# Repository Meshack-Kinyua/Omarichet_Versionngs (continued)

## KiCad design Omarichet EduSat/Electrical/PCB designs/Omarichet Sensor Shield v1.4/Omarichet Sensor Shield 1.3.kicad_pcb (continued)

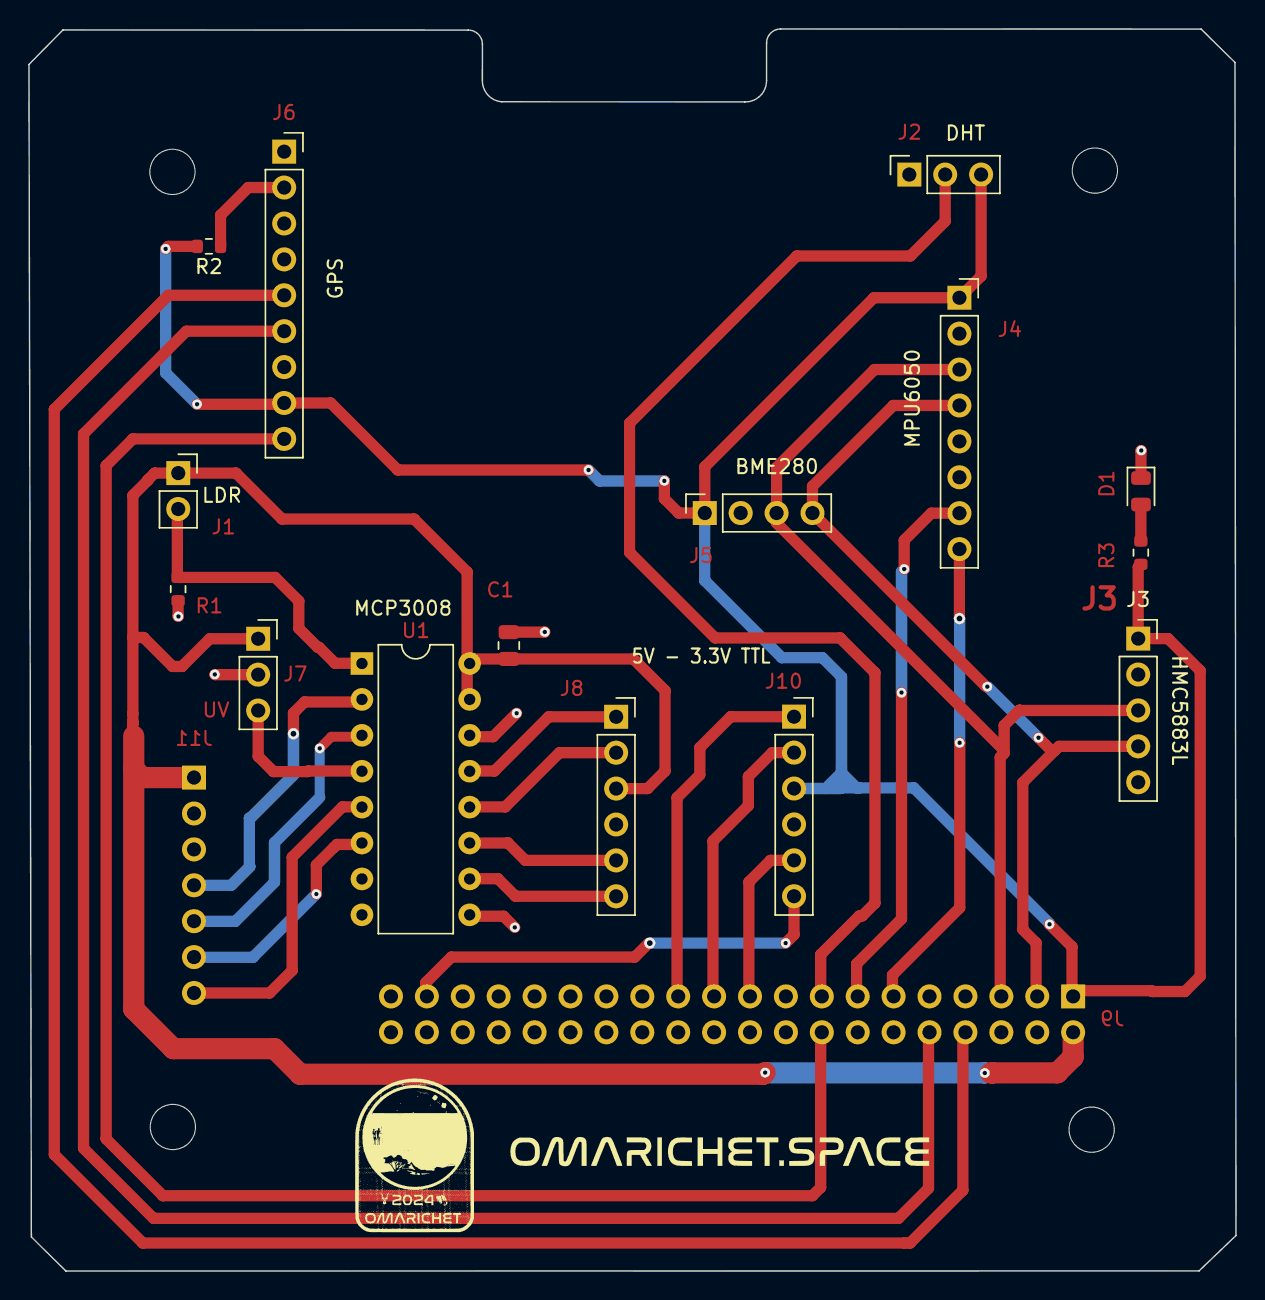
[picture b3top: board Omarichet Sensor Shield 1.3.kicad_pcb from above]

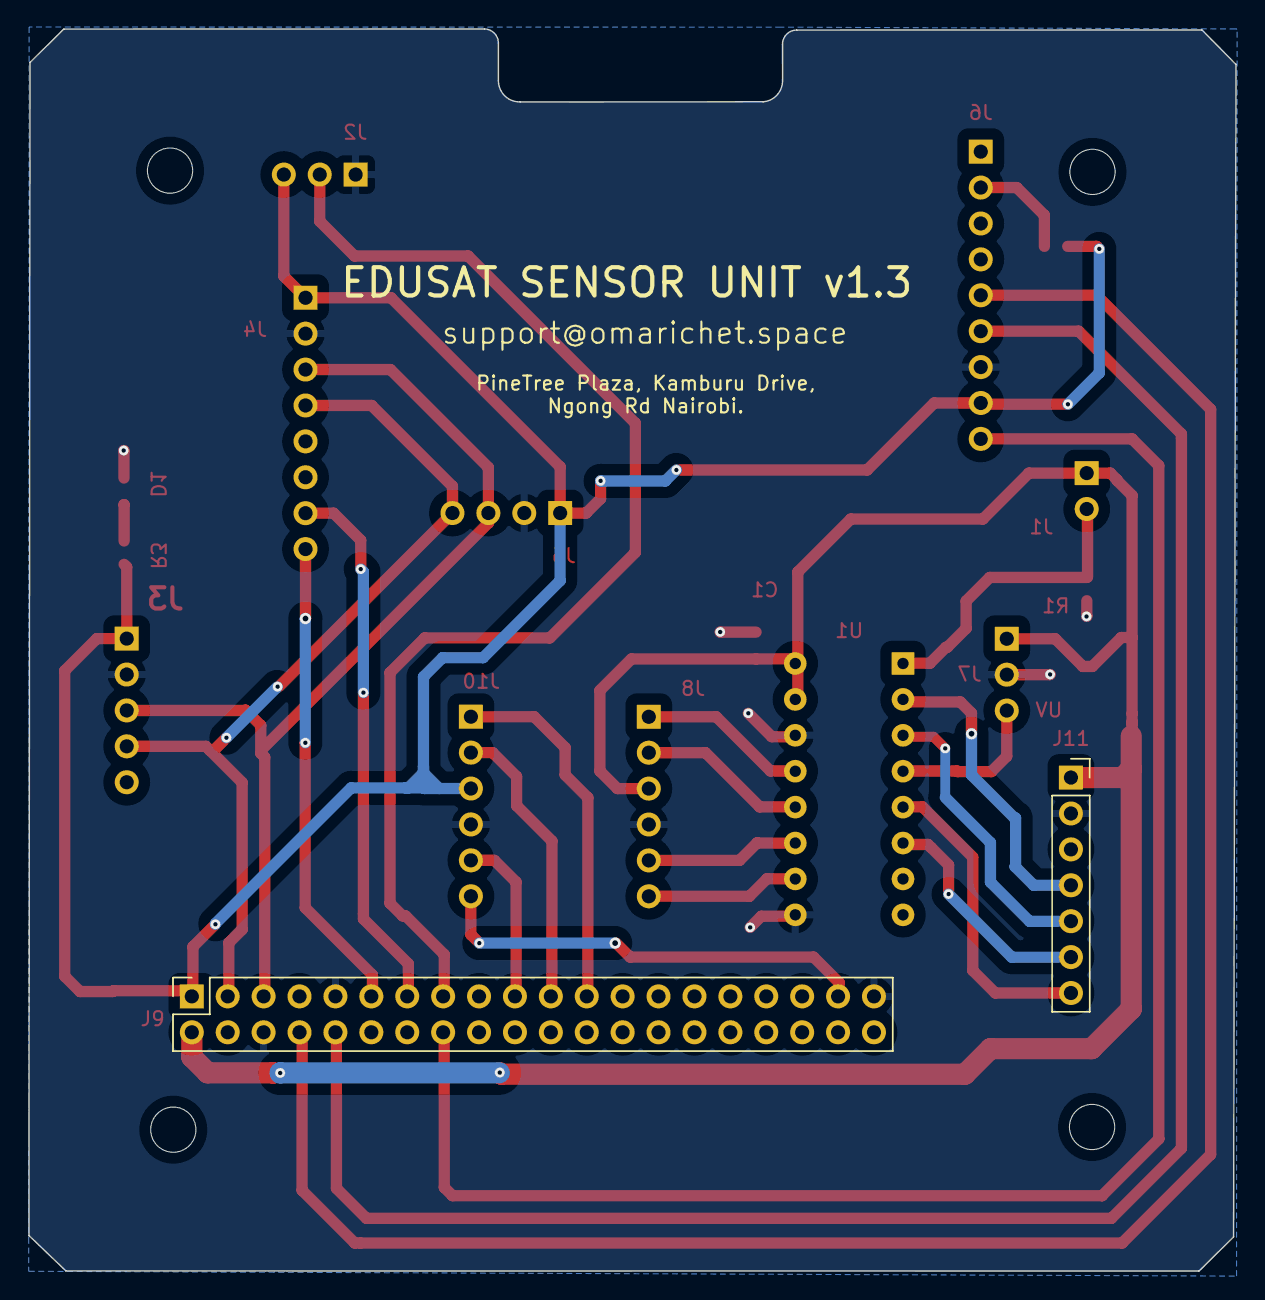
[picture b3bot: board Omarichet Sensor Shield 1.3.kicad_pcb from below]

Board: 2 copper layers, 85.4 x 87.9 mm, 21 parts (2 on the bottom side), 27 nets.

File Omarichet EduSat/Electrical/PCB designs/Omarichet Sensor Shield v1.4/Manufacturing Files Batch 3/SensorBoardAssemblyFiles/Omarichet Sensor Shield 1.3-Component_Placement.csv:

Ref,Val,Package,PosX,PosY,Rot,Side
"J9","Conn_02x20_Odd_Even","PinSocket_2x20_P2.54mm_Vertical",-159.670000,-129.990000,90.000000,bottom
"J11","Conn_01x07_Female","PinSocket_1x07_P2.54mm_Vertical",-97.475000,-114.510000,180.000000,bottom
"C1","100n","C_0805_2012Metric",119.750000,-105.170000,90.000000,top
"D1","LED","LED_0805_2012Metric",164.470000,-94.257500,-90.000000,top
"J1","Conn_01x02_Light","PinSocket_1x02_P2.54mm_Vertical",96.360000,-92.970000,0.000000,top
"J2","Conn_01x03_DHT","PinSocket_1x03_P2.54mm_Vertical",148.080000,-71.850000,90.000000,top
"J3","Conn_01x05_HMC5883L","PinSocket_1x05_P2.54mm_Vertical",164.275000,-104.680000,0.000000,top
"J4","Conn_01x08_mpu6050","PinSocket_1x08_P2.54mm_Vertical",151.625000,-80.565000,0.000000,top
"J5","Conn_01x04_BME280","PinSocket_1x04_P2.54mm_Vertical",133.610000,-95.795000,90.000000,top
"J6","Conn_01x09_GPS","PinSocket_1x09_P2.54mm_Vertical",103.855000,-70.230000,0.000000,top
"J7","Conn_01x03_GUVA-S12SD","PinSocket_1x03_P2.54mm_Vertical",102.015000,-104.690000,0.000000,top
"J8","Conn_01x06_LLCA","PinSocket_1x06_P2.54mm_Vertical",127.340000,-110.210000,0.000000,top
"J10","Conn_01x06_LLCB","PinSocket_1x06_P2.54mm_Vertical",139.925000,-110.205000,0.000000,top
"R1","10k","R_0603_1608Metric",96.350000,-101.175000,-90.000000,top
"R2","10K","R_0603_1608Metric",98.530000,-76.930000,180.000000,top
"R3","R","R_0603_1608Metric",164.460000,-98.600000,90.000000,top
"U1","MCP3008","DIP-16_W7.62mm",109.356000,-106.441000,0.000000,top

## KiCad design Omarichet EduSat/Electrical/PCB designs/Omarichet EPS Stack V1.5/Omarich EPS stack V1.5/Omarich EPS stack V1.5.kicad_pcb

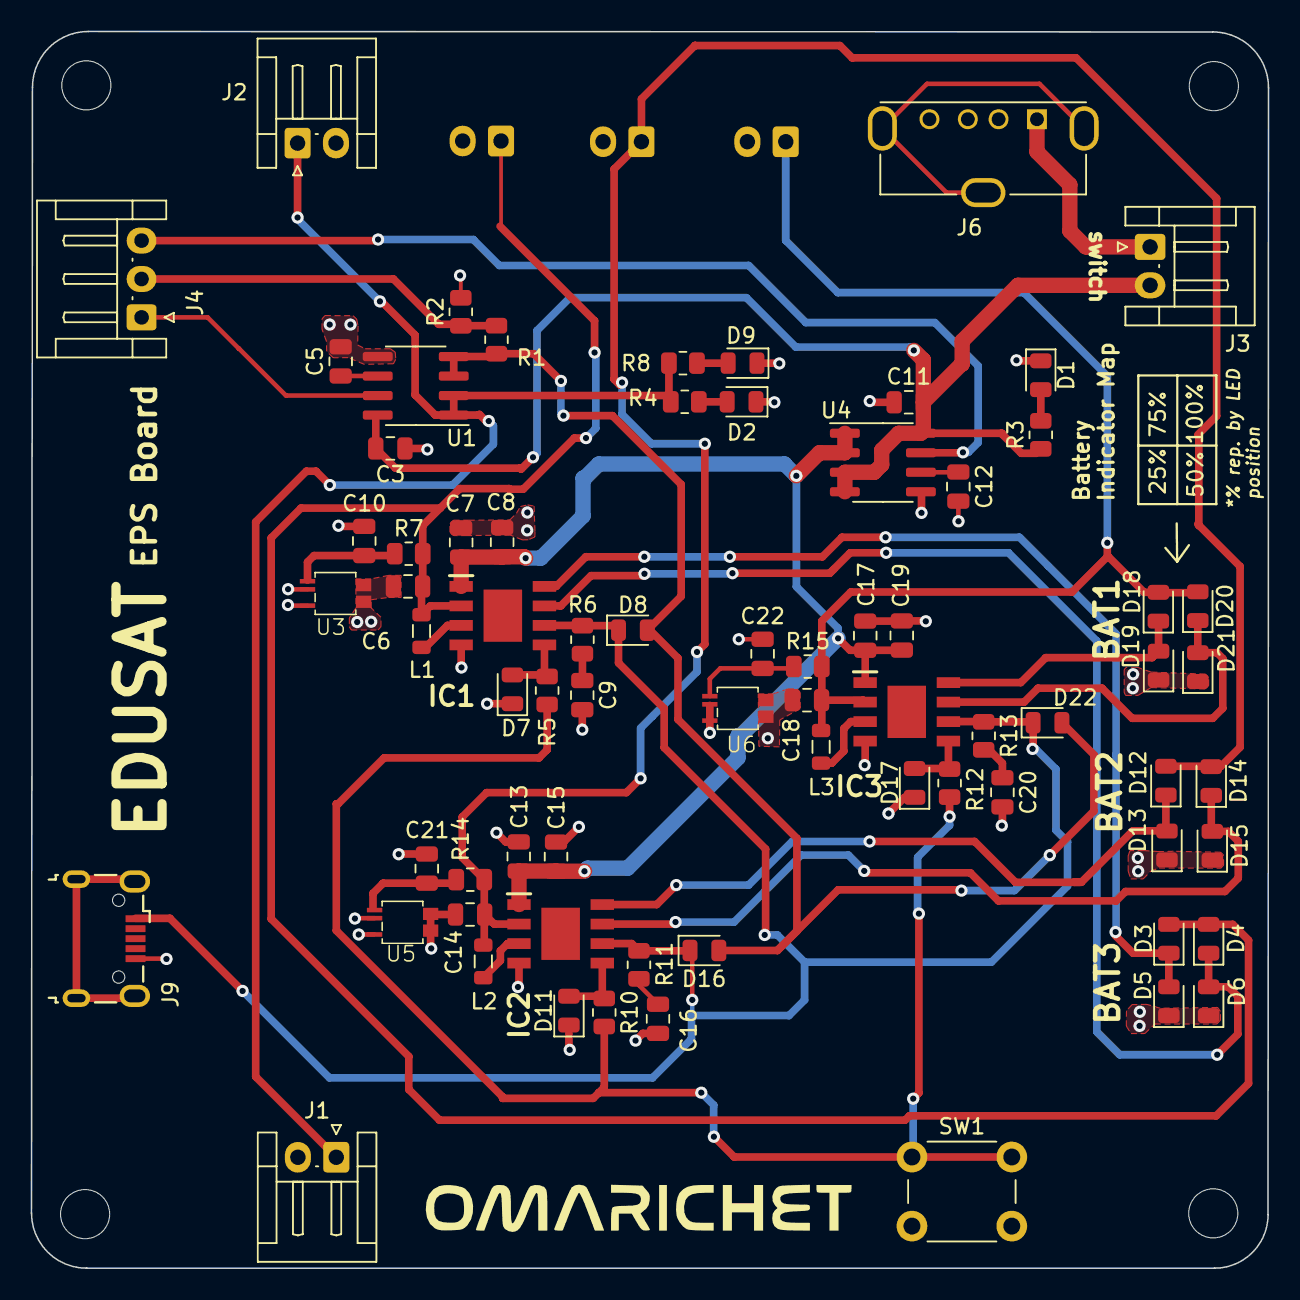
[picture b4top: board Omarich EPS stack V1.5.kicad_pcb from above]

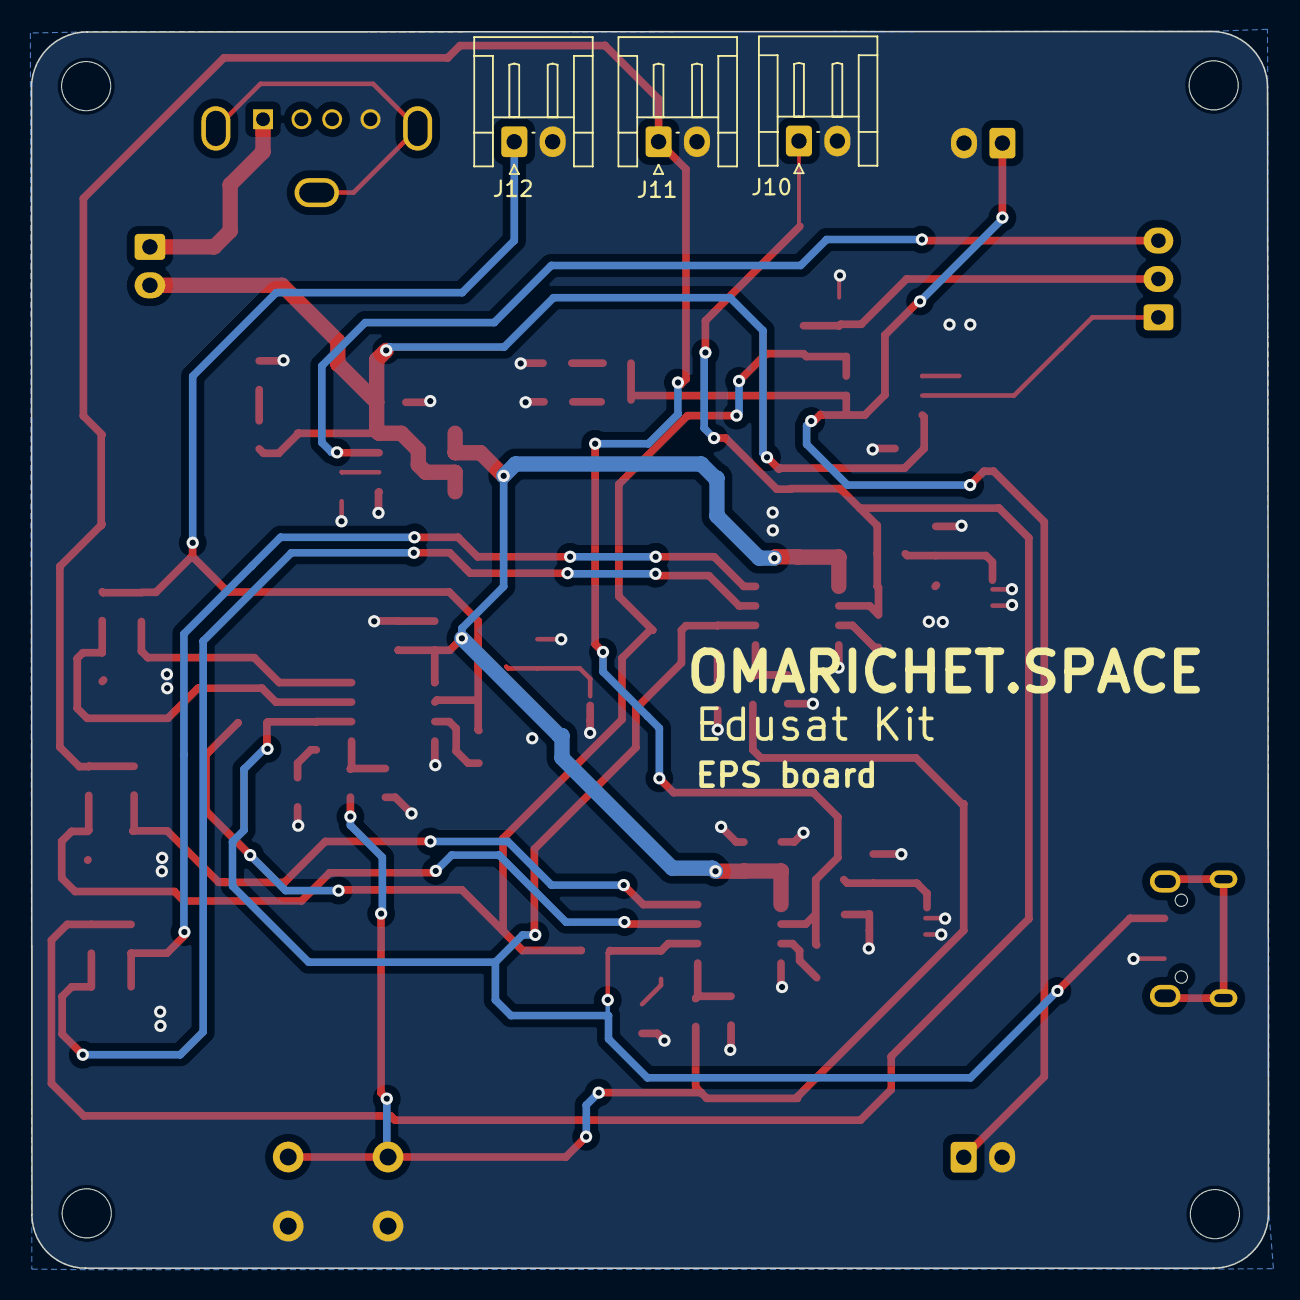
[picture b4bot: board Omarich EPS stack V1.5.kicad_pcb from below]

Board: 2 copper layers, 80.6 x 80.5 mm, 79 parts (3 on the bottom side), 37 nets.

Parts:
C3, C5, C11, C12: 1nF; C_0805_2012Metric
C6, C7, C8, C13, C14, C15, C17, C18, C19: 10uF; C_0805_2012Metric
C9, C16, C20: 2.2uF; C_0805_2012Metric
C10, C21, C22: 0.1uF; C_0805_2012Metric
D1, D2, D3, D4, D5, D6, D7, D9, D11, D12, D13, D14, D15, D17, D18, D19, D20, D21: LED; LED_0805_2012Metric
D8, D16, D22: D; D_0805_2012Metric
H1, H2, H3, H4: MountingHole; MountingHole_3.2mm_M3
IC1, IC2, IC3: TP4366E
J1, J2, J3, J10, J11, J12: Conn_01x02_Pin; JST_EH_S2B-EH_1x02_P2.50mm_Horizontal
J4: Conn_01x03_Pin; JST_EH_S3B-EH_1x03_P2.50mm_Horizontal
J6: USB_A; USB_A_Molex_105057_Vertical
J9: USB_B_Micro; USB_Micro-B_Wuerth_629105150521
L1, L2, L3: 1.5uH; L_0805_2012Metric
R1: 7.5k; R_0805_2012Metric
R2: 30k; R_0805_2012Metric
R3, R4, R7, R8, R14, R15: 1k; R_0805_2012Metric
R5, R10, R12: 10K; R_0805_2012Metric
R6, R11, R13: 1k5; R_0805_2012Metric
SW1: SW_Push; SW_PUSH_6mm_H5mm
U1, U4: ACS712xLCTR-05B; SOIC-8_3.9x4.9mm_P1.27mm
U3, U5, U6: XB7608AJ

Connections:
5V: C7.2, C8.2, C13.2, C15.2, C17.2, C19.2, IC1.1 (OUT), IC2.1 (OUT), IC3.1 (OUT), U4.1 (IP+), U4.2 (IP+)
+5V: C3.2, C11.2, J3.2, R3.1, U1.8 (VCC), U4.3 (IP-), U4.4 (IP-), U4.8 (VCC)
/SWT1: D7.2 (A), IC1.5 (SWT), R5.1
/SWT2: D11.2 (A), IC2.5 (SWT), R10.1
/SWT3: D17.2 (A), IC3.5 (SWT), R12.1
BAT-1: C6.1, D3.2 (A), D4.2 (A), IC1.2 (BAT), J10.1, L1.1, R7.2
BAT-2: C14.1, D12.2 (A), D14.2 (A), IC2.2 (BAT), J11.1, L2.1, R14.2
BAT-3: C18.1, D18.2 (A), D20.2 (A), IC3.2 (BAT), J12.1, L3.1, R15.2
BtnIn: R5.2, R10.2, R12.2, SW1.1
CH3: J4.3, U4.7 (VIOUT)
CH4: J4.2, R1.2, R2.1
CH5: J4.1, U1.7 (VIOUT)
GND: C3.1, C5.2, C6.2, C7.1, C8.1, C9.2, C10.2, C11.1, C12.2, C13.1, C14.2, C15.1, C16.2, C17.1, C18.2, C19.1, C20.2, C21.2, C22.2, D1.1 (K), D2.1 (K), D5.1 (K), D6.1 (K), D7.1 (K), D9.1 (K), D11.1 (K), D13.1 (K), D15.1 (K), D17.1 (K), D19.1 (K), D21.1 (K), IC1.4 (GND), IC2.4 (GND), IC3.4 (GND), J1.2, J2.2, J6.4 (GND), J9.5 (GND), J10.2, J11.2, J12.2, R2.2, SW1.2, U1.5 (GND), U3.2 (GND), U3.3 (GND), U3.4 (VM), U3.5 (VM), U4.5 (GND), U5.2 (GND), U5.3 (GND), U5.4 (VM), U5.5 (VM), U6.2 (GND), U6.3 (GND), U6.4 (VM), U6.5 (VM)
unnamed: C9.1, R6.2
unnamed: C16.1, R11.2
unnamed: C20.1, R13.2
unnamed: D1.2 (A), R3.2
unnamed: D2.2 (A), R4.2
unnamed: D3.1 (K), D5.2 (A), IC1.8 (LED1)
unnamed: D4.1 (K), D6.2 (A), IC1.7 (LED2)
unnamed: D9.2 (A), R8.2
unnamed: D12.1 (K), D13.2 (A), IC2.8 (LED1)
unnamed: D14.1 (K), D15.2 (A), IC2.7 (LED2)
unnamed: D18.1 (K), D19.2 (A), IC3.8 (LED1)
unnamed: D20.1 (K), D21.2 (A), IC3.7 (LED2)
unnamed: J3.1, J6.1 (VBUS)
unnamed: C5.1, U1.6 (FILTER)
unnamed: C10.1, R7.1, U3.1 (VDD)
unnamed: C12.1, U4.6 (FILTER)
unnamed: C21.1, R14.1, U5.1 (VDD)
unnamed: C22.1, R15.1, U6.1 (VDD)
SW1: IC1.3 (SW), L1.2
SW2: IC2.3 (SW), L2.2
SW3: IC3.3 (SW), L3.2
Solar1: J1.1, J2.1, R4.1, R8.1, U1.1 (IP+), U1.2 (IP+)
VBUS: D8.1 (K), D16.1 (K), D22.1 (K), IC1.6 (VDD), IC2.6 (VDD), IC3.6 (VDD), J9.1 (VBUS), R6.1, R11.1, R13.1
VDD: D8.2 (A), D16.2 (A), D22.2 (A), R1.1, U1.3 (IP-), U1.4 (IP-)

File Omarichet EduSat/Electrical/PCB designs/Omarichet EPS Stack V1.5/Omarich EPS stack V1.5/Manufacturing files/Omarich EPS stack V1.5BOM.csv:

"Source:","/home/gerald/systems/School-Edusat/Electrical/PCB designs/Omarichet EPS Stack V1.5/Omarich EPS stack V1.5/Omarich EPS stack V1.5.kicad_sch"
"Date:","Fri 06 Oct 2023 08:44:06 AM EAT"
"Tool:","Eeschema 7.0.8-7.0.8~ubuntu22.04.1"
"Generator:","/usr/share/kicad/plugins/bom_csv_grouped_by_value_with_fp.py"
"Component Count:","79"
"Ref","Qnty","Value","Cmp name","Footprint","Description","Vendor","DNP"
"C3, C5, C11, C12","4","1nF","C","Capacitor_SMD:C_0805_2012Metric","Unpolarized capacitor","",""
"C6, C7, C8, C13, C14, C15, C17, C18, C19","9","10uF","C","Capacitor_SMD:C_0805_2012Metric","Unpolarized capacitor","",""
"C9, C16, C20","3","2.2uF","C","Capacitor_SMD:C_0805_2012Metric","Unpolarized capacitor","",""
"C10, C21, C22","3","0.1uF","C","Capacitor_SMD:C_0805_2012Metric","Unpolarized capacitor","",""
"D1, D2, D3, D4, D5, D6, D7, D9, D11, D12, D13, D14, D15, D17, D18, D19, D20, D21","18","LED","LED","LED_SMD:LED_0805_2012Metric","Light emitting diode","",""
"D8, D16, D22","3","D","D","Diode_SMD:D_0805_2012Metric","Diode","",""
"H1, H2, H3, H4","4","MountingHole","MountingHole","MountingHole:MountingHole_3.2mm_M3","Mounting Hole without connection","",""
"IC1, IC2, IC3","3","TP4366E","TP4366E","TP4366E:TP4366E","1A synchronous mobile power solution","",""
"J1, J2, J3, J10, J11, J12","6","Conn_01x02_Pin","Conn_01x02_Pin","Connector_JST:JST_EH_S2B-EH_1x02_P2.50mm_Horizontal","Generic connector, single row, 01x02, script generated","",""
"J4","1","Conn_01x03_Pin","Conn_01x03_Pin","Connector_JST:JST_EH_S3B-EH_1x03_P2.50mm_Horizontal","Generic connector, single row, 01x03, script generated","",""
"J6","1","USB_A","USB_A","Connector_USB:USB_A_Molex_105057_Vertical","USB Type A connector","",""
"J9","1","USB_B_Micro","USB_B_Micro","Connector_USB:USB_Micro-B_Wuerth_629105150521","USB Micro Type B connector","",""
"L1, L2, L3","3","1.5uH","L","Inductor_SMD:L_0805_2012Metric","Inductor","",""
"R1","1","7.5k","R","Resistor_SMD:R_0805_2012Metric","Resistor","",""
"R2","1","30k","R","Resistor_SMD:R_0805_2012Metric","Resistor","",""
"R3, R4, R7, R8, R14, R15","6","1k","R","Resistor_SMD:R_0805_2012Metric","Resistor","",""
"R5, R10, R12","3","10K","R","Resistor_SMD:R_0805_2012Metric","Resistor","",""
"R6, R11, R13","3","1k5","R","Resistor_SMD:R_0805_2012Metric","Resistor","",""
"SW1","1","SW_Push","SW_Push","Button_Switch_THT:SW_PUSH_6mm_H5mm","Push button switch, generic, two pins","",""
"U1, U4","2","ACS712xLCTR-05B","ACS712xLCTR-05B","Package_SO:SOIC-8_3.9x4.9mm_P1.27mm","±5A Bidirectional Hall-Effect Current Sensor, +5.0V supply, 185mV/A, SOIC-8","",""
"U3, U5, U6","3","~","XB7608A","XBAJ:XB7608AJ","One Cell Lithium-ion/Polymer Battery Protection IC","",""

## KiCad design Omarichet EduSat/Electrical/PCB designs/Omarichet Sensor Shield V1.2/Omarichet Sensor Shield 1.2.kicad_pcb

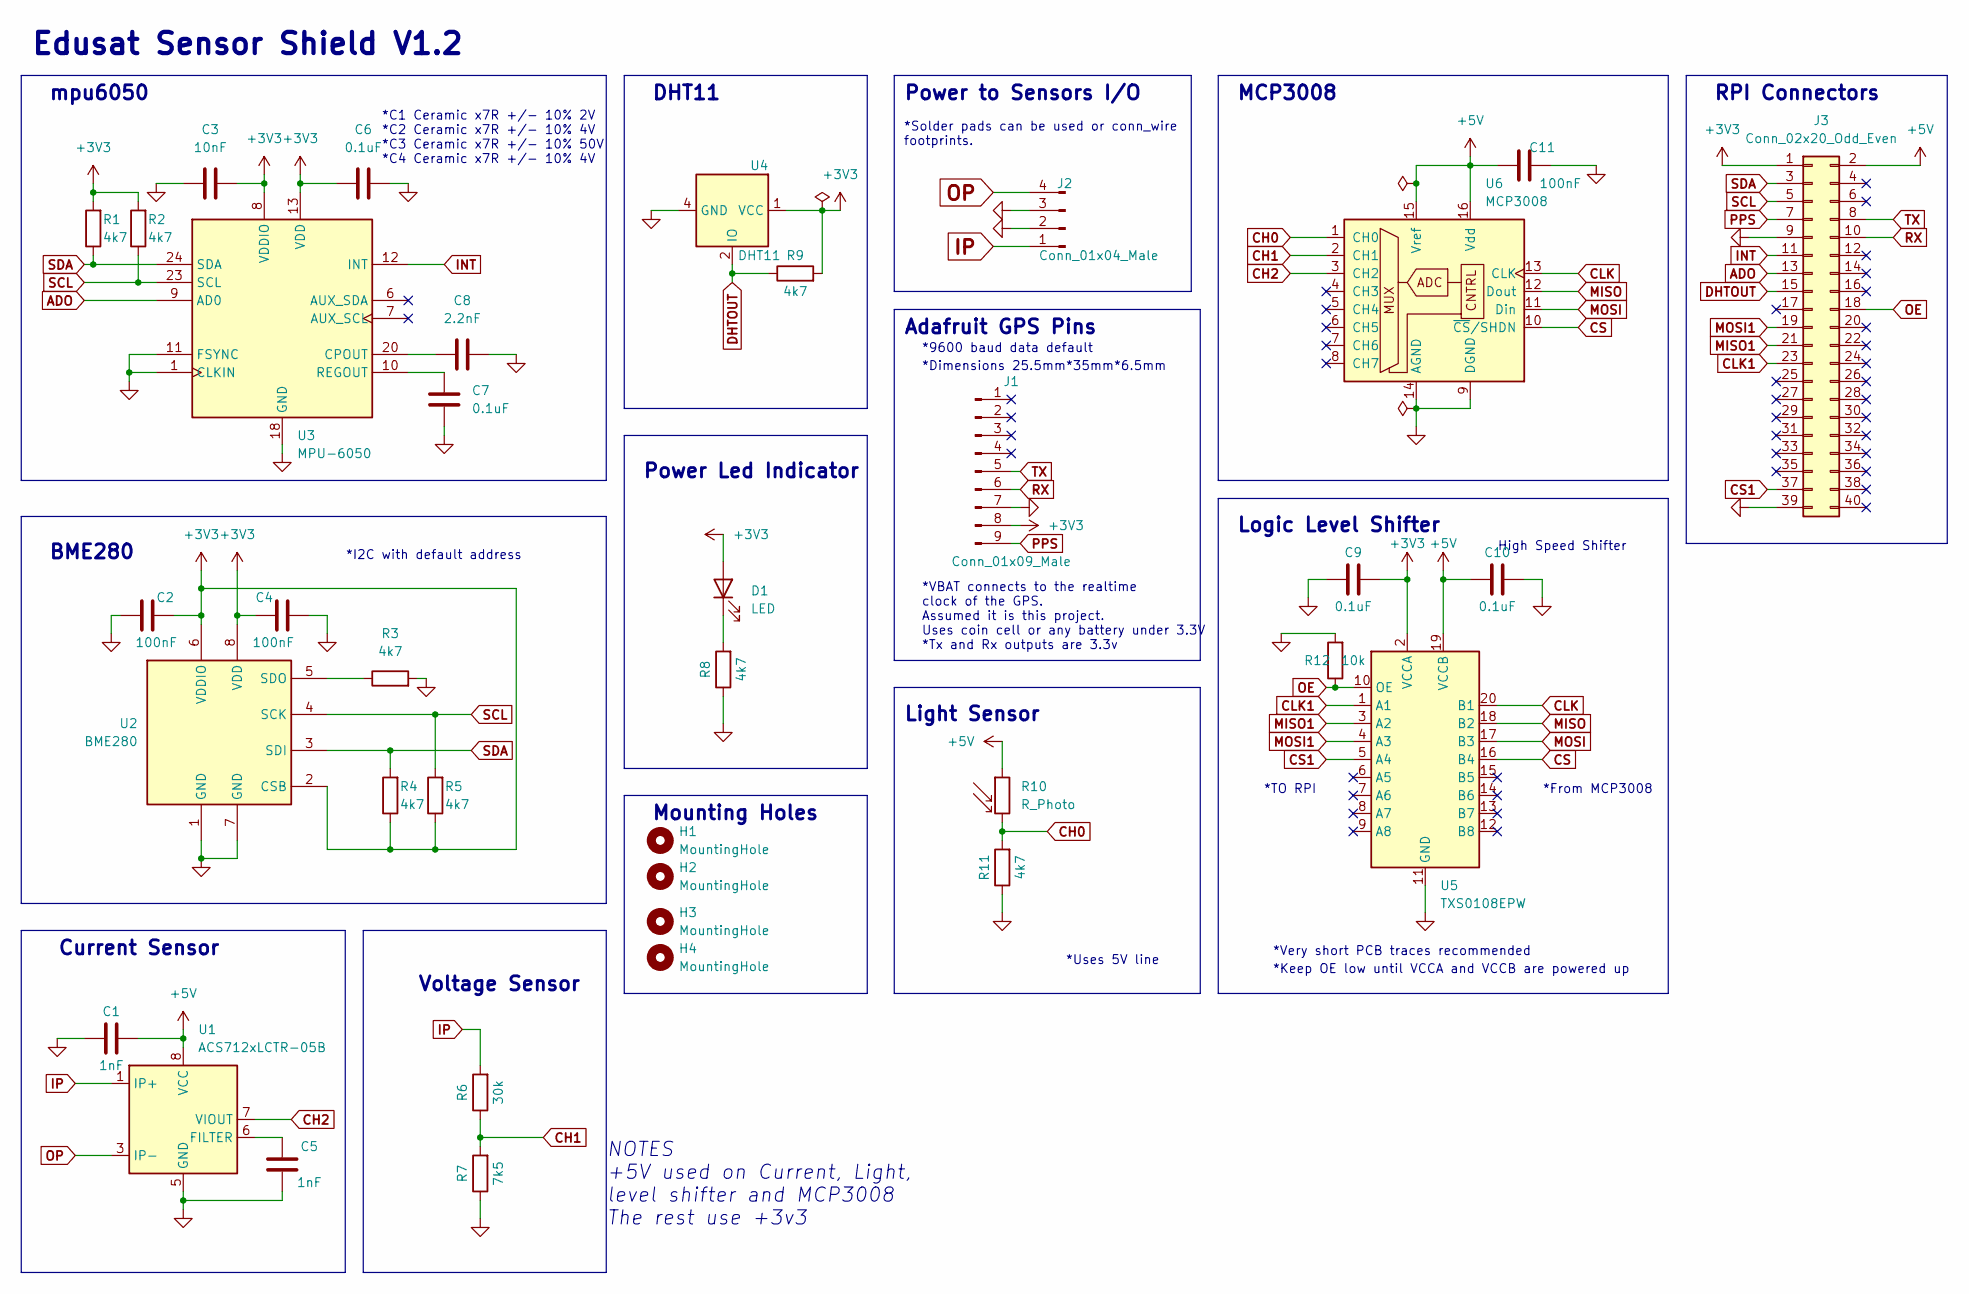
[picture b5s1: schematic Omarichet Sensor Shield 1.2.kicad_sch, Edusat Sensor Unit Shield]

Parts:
C1, C5: 1nF; C_0402_1005Metric
C2, C4, C11: 100nF; C_0402_1005Metric
C3: 10nF; C_0402_1005Metric
C6, C7, C9, C10: 0.1uF; C_0603_1608Metric
C8: 2.2nF; C_0402_1005Metric
D1: LED; LED_0603_1608Metric
H1, H2, H3, H4: MountingHole; MountingHole_3.2mm_M3
J1: Conn_01x09_Male; PinHeader_1x09_P2.54mm_Vertical
J2: Conn_01x04_Male; SolderWire-0.25sqmm_1x04_P4.2mm_D0.65mm_OD1.7mm_Relief
J3: Conn_02x20_Odd_Even; PinSocket_2x20_P2.54mm_Vertical
R1, R2, R3, R4, R5, R8, R9, R11: 4k7; R_0402_1005Metric
R6: 30k; R_0402_1005Metric
R7: 7k5; R_0402_1005Metric
R10: R_Photo; R_LDR_4.9x4.2mm_P2.54mm_Vertical
R12: 10k; R_0402_1005Metric
U1: ACS712xLCTR-05B; SOIC-8_3.9x4.9mm_P1.27mm
U2: BME280; Bosch_LGA-8_2.5x2.5mm_P0.65mm_ClockwisePinNumbering
U3: MPU-6050; InvenSense_QFN-24_4x4mm_P0.5mm
U4: DHT11; Aosong_DHT11_5.5x12.0_P2.54mm
U5: TXS0108EPW; TSSOP-20_4.4x6.5mm_P0.65mm
U6: MCP3008; DIP-16_W7.62mm

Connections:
+3V3: C2.2, C3.2, C4.1, C6.1, C9.2, D1.2 (A), J1.8, J3.1, R1.2, R2.2, R4.1, R5.1, R9.2, U2.2 (CSB), U2.6 (VDDIO), U2.8 (VDD), U3.8 (VDDIO), U3.13 (VDD), U4.1 (VCC), U5.2 (VCCA)
+5V: C1.1, C10.1, C11.1, J3.2, R10.1, U1.8 (VCC), U5.19 (VCCB), U6.15 (Vref), U6.16 (Vdd)
ADO: J3.13, U3.9 (AD0)
CH0: R10.2, R11.2, U6.1 (CH0)
CH1: R6.1, R7.2, U6.2 (CH1)
CH2: U1.7 (VIOUT), U6.3 (CH2)
CLK: U5.20 (B1), U6.13 (CLK)
CLK1: J3.23, U5.1 (A1)
CS: U5.16 (B4), U6.10 (~CS/SHDN)
CS1: J3.37, U5.5 (A4)
DHTOUT: J3.15, R9.1, U4.2 (IO)
GND: C1.2, C2.1, C3.1, C4.2, C5.1, C6.2, C7.1, C8.2, C9.1, C10.2, C11.2, J1.7, J2.2, J2.3, J3.9, J3.39, R3.2, R7.1, R8.1, R11.1, R12.2, U1.5 (GND), U2.1 (GND), U2.7 (GND), U3.1 (CLKIN), U3.11 (FSYNC), U3.18 (GND), U4.4 (GND), U5.11 (GND), U6.9 (DGND), U6.14 (AGND)
INT: J3.11, U3.12 (INT)
IP: J2.1, R6.2, U1.1 (IP+), U1.2 (IP+)
MISO: U5.18 (B2), U6.12 (Dout)
MISO1: J3.21, U5.3 (A2)
MOSI: U5.17 (B3), U6.11 (Din)
MOSI1: J3.19, U5.4 (A3)
unnamed: C5.2, U1.6 (FILTER)
unnamed: C7.2, U3.10 (REGOUT)
unnamed: C8.1, U3.20 (CPOUT)
unnamed: D1.1 (K), R8.2
unnamed: R3.1, U2.5 (SDO)
OE: J3.18, R12.1, U5.10 (OE)
OP: J2.4, U1.3 (IP-), U1.4 (IP-)
PPS: J1.9, J3.7
RX: J1.6, J3.10
SCL: J3.5, R2.1, R5.2, U2.4 (SCK), U3.23 (SCL)
SDA: J3.3, R1.1, R4.2, U2.3 (SDI), U3.24 (SDA)
TX: J1.5, J3.8

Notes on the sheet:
Voltage Sensor
DHT11
MCP3008
*Keep OE low until VCCA and VCCB are powered up
*Dimensions 25.5mm*35mm*6.5mm
Power Led Indicator
*9600 baud data default
Mounting Holes
Light Sensor
BME280
RPI Connectors
Edusat Sensor Shield V1.2
*TO RPI
Adafruit GPS Pins
*Very short PCB traces recommended
Current Sensor
Power to Sensors I/O
*Solder pads can be used or conn_wire footprints.
*VBAT connects to the realtime clock of the GPS. Assumed it is this project. Uses coin cell or any battery under 3.3V *Tx and Rx outputs are 3.3v
NOTES +5V used on Current, Light, level shifter and MCP3008 The rest use +3v3
mpu6050
*Uses 5V line
Logic Level Shifter
*C1 Ceramic x7R +/- 10% 2V *C2 Ceramic x7R +/- 10% 4V *C3 Ceramic x7R +/- 10% 50V *C4 Ceramic x7R +/- 10% 4V
*From MCP3008
High Speed Shifter
*I2C with default address

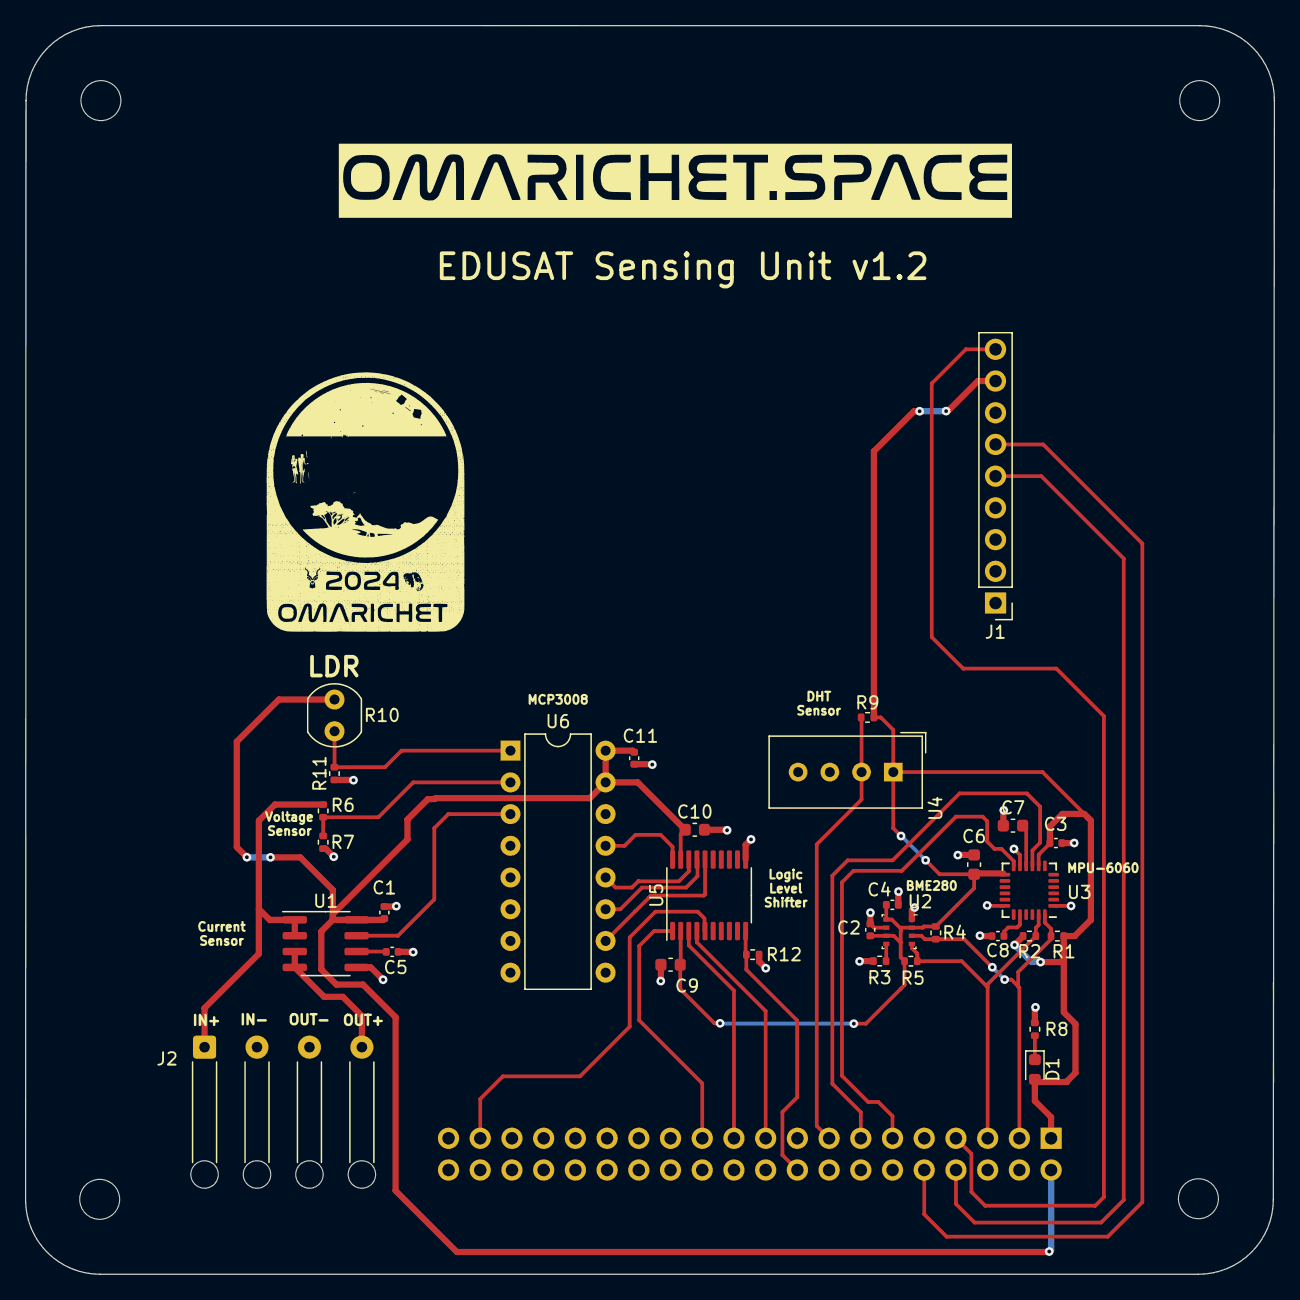
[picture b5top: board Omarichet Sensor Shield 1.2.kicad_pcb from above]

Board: 2 copper layers, 100.0 x 100.0 mm, 37 parts (1 on the bottom side), 30 nets.

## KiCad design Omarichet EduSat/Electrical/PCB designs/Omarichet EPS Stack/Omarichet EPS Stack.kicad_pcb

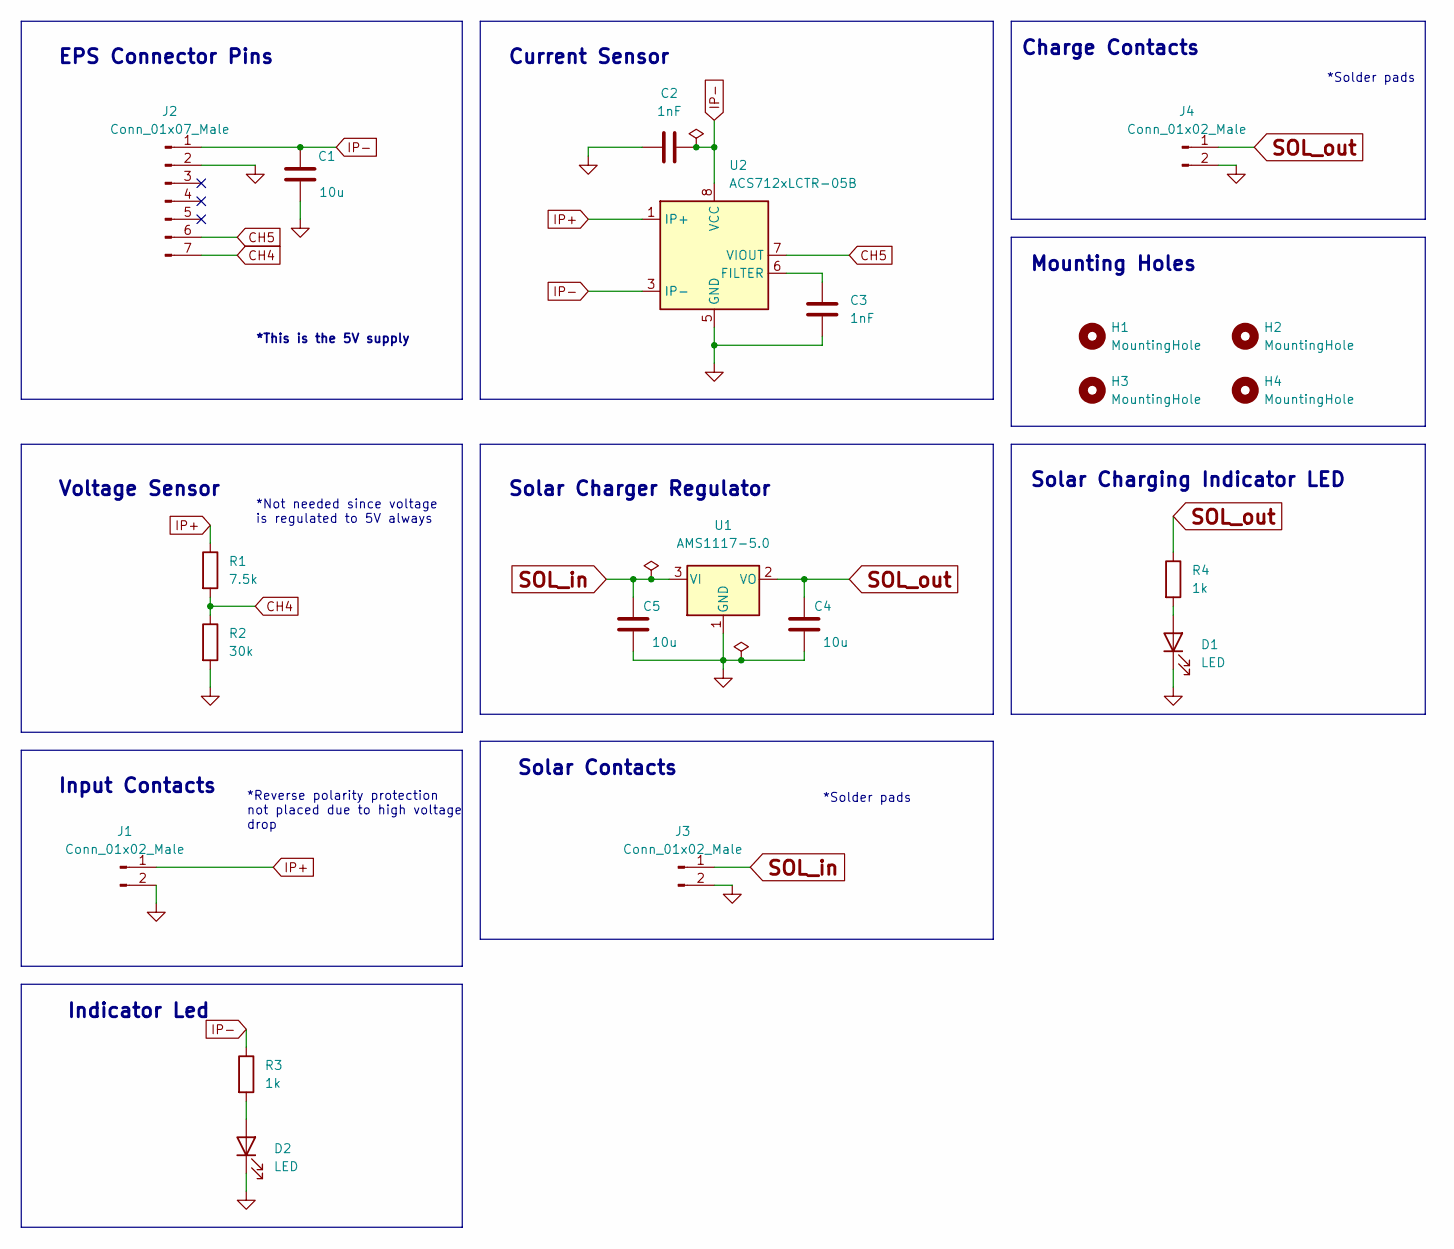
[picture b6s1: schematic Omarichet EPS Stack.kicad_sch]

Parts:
C1, C4, C5: 10u; C_0805_2012Metric
C2, C3: 1nF; C_0805_2012Metric
D1, D2: LED; LED_0805_2012Metric
H1, H2, H3, H4: MountingHole; MountingHole_3.2mm_M3
J1, J3, J4: Conn_01x02_Male; SolderWire-0.75sqmm_1x02_P7mm_D1.25mm_OD3.5mm_Relief
J2: Conn_01x07_Male; PinHeader_1x07_P2.54mm_Vertical
R1: 7.5k; R_0603_1608Metric
R2: 30k; R_0603_1608Metric
R3, R4: 1k; R_0603_1608Metric
U1: AMS1117-5.0; SOT-223-3_TabPin2
U2: ACS712xLCTR-05B; SOIC-8_3.9x4.9mm_P1.27mm

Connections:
CH4: J2.7, R1.2, R2.1
CH5: J2.6, U2.7 (VIOUT)
GND: C1.1, C2.1, C3.2, C4.2, C5.2, D1.1 (K), D2.1 (K), J1.2, J2.2, J3.2, J4.2, R2.2, U1.1 (GND), U2.5 (GND)
IP+: J1.1, R1.1, U2.1 (IP+), U2.2 (IP+)
IP-: C1.2, C2.2, J2.1, R3.1, U2.3 (IP-), U2.4 (IP-), U2.8 (VCC)
unnamed: C3.1, U2.6 (FILTER)
unnamed: D1.2 (A), R4.2
unnamed: D2.2 (A), R3.2
SOL_in: C5.1, J3.1, U1.3 (VI)
SOL_out: C4.1, J4.1, R4.1, U1.2 (VO)

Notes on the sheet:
Solar Charging Indicator LED
*Not needed since voltage is regulated to 5V always
*This is the 5V supply
Indicator Led
*Solder pads
Charge Contacts
Solar Charger Regulator
Solar Contacts
Input Contacts
*Reverse polarity protection not placed due to high voltage drop
Mounting Holes
Current Sensor
Voltage Sensor
EPS Connector Pins

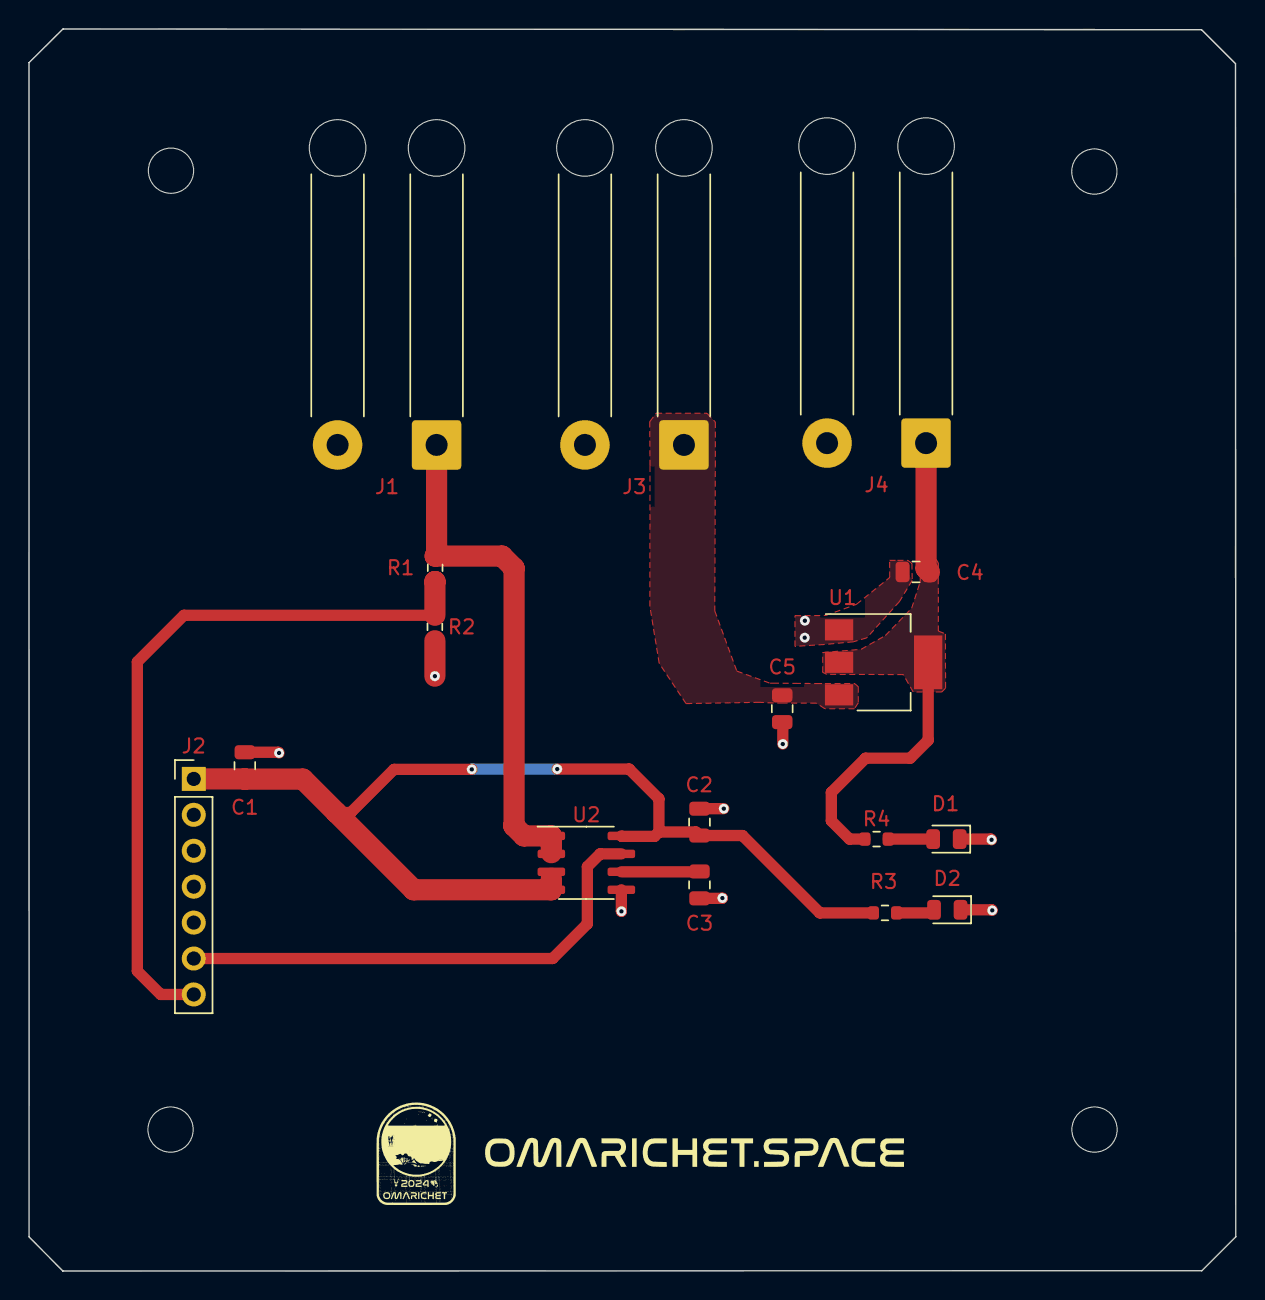
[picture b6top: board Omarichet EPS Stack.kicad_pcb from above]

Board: 2 copper layers, 85.3 x 87.8 mm, 21 parts (0 on the bottom side), 10 nets.

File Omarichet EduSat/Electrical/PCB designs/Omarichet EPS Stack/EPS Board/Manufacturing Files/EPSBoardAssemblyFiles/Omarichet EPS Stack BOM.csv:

Source:,D:\systems\school_Edusat\School-Edusat\Electrical\PCB designs\Omarichet EPS Stack\Omarichet EPS Stack.kicad_sch,,,,,
,,,,,,
Date:,21/02/2023 13:05,,,,,
,,,,,,
Tool:,Eeschema (6.0.7),,,,,
,,,,,,
Generator:,C:\Program Files\KiCad\6.0\bin\scripting\plugins/bom_csv_grouped_by_value_with_fp.py,,,,,
,,,,,,
Component Count:,21,,,,,
,,,,,,
Ref,Qnty,Value,Cmp name,Footprint,Description,Vendor
,,,,,,
"C1, C4, C5, ",3,10u,C,Capacitor_SMD:C_0805_2012Metric,Unpolarized capacitor,
,,,,,,
"C2, C3, ",2,1nF,C,Capacitor_SMD:C_0805_2012Metric,Unpolarized capacitor,
,,,,,,
"D1, D2, ",2,LED,LED,LED_SMD:LED_0805_2012Metric,Light emitting diode,
,,,,,,
"R1, ",1,7.5k,R,Resistor_SMD:R_0603_1608Metric,Resistor,
,,,,,,
"R2, ",1,30k,R,Resistor_SMD:R_0603_1608Metric,Resistor,
,,,,,,
"R3, R4, ",2,1k,R,Resistor_SMD:R_0603_1608Metric,Resistor,
,,,,,,
"U1, ",1,AMS1117-5.0,AMS1117-5.0,Package_TO_SOT_SMD:SOT-223-3_TabPin2,"1A Low Dropout regulator, positive, 5.0V fixed output, SOT-223",
,,,,,,
"U2, ",1,ACS712xLCTR-05B,ACS712xLCTR-05B,Package_SO:SOIC-8_3.9x4.9mm_P1.27mm,"±5A Bidirectional Hall-Effect Current Sensor, +5.0V supply, 185mV/A, SOIC-8",
